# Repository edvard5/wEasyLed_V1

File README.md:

# Addressable RGB LED Controller PCB for WLED

This is a custom PCB designed for controlling addressable RGB LED lights using [WLED](https://github.com/Aircoookie/WLED). The board supports both 5V and 12V LEDs, making it versatile for various setups. It is compact, reliable, and optimized for seamless integration with WLED firmware.

## Features
- Compatible with WLED firmware.
- Supports addressable LEDs (e.g., WS2812, SK6812).
- Integrated voltage regulation for 5V and 12V operation.
- Compact layout with easy connections for power and data.

## Documentation

### PCB Layout

### Schematic

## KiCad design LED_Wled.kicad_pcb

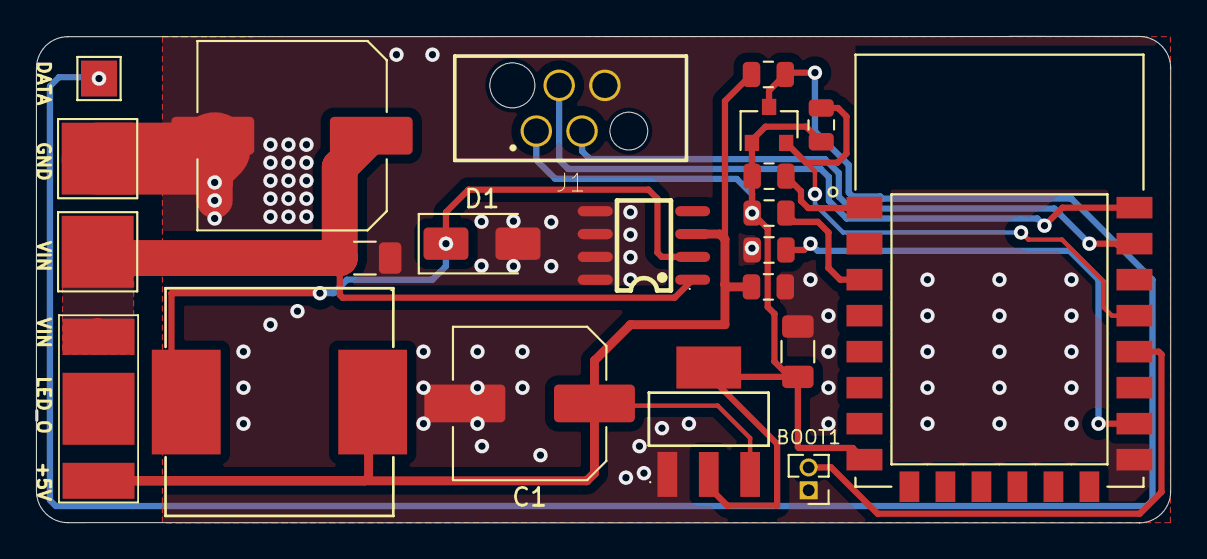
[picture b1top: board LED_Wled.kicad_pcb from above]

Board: 2 copper layers, 63.0 x 27.0 mm, 23 parts (1 on the bottom side), 13 nets.

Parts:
BOOT1: Jumper; PinHeader_1x02_P1.27mm_Vertical
C1: 220uF/35V; C_Elec_8x10.2
C2: 470uF/35V; C_Elec_10x10.2
C3: 1uF/50V; C_1206_3216Metric
C4: 100nF/50V; C_0805_2012Metric
C5: 10uF/50V; C_1206_3216Metric
D1: SS54; D_SMA
J1: SWD_PORT_SKEDD; WR_WST_REDFIT_IDC_4Pin
J2, J4: Conn_01x01; TestPoint_Pad_4.0x4.0mm
J3: Conn_01x01; TestPoint_Pad_2.0x2.0mm
JP1: SolderJumper_3_Open; BIG JUMPER
L1: 68uH; IND-SMD_L12.5-W12.5
Q1: 2N7002; SOT-23
R1, R2, R3, R4, R5: 10k; R_0805_2012Metric
SYM1: LOGO; easyled
U1: ESP8266-12E_ESP-12E; ESP-12E
U2: XL1509; SOIC-8_L5.0-W4.0-P1.27-LS6.0-BL
U3: AMS1117-3.3; SOT-223-3_L6.5-W3.4-P2.30-LS7.0-BR

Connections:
+3V3: C5.1, J1.1, Q1.1 (G), R1.1, R2.2, R4.1, U1.8 (VCC), U3.2 (VOUT), U3.4 (VOUT)
+5V: C1.1, C4.1, JP1.3 (B), L1.2, R5.1, U2.3 (FB), U3.3 (VIN)
GND: BOOT1.1 (A), C1.2, C2.2, C3.2, C4.2, C5.2, D1.2 (A), J1.4, J4.1, R3.2, U1.15 (GND), U2.5 (GND), U2.6 (GND), U2.7 (GND), U2.8 (GND), U3.1 (GND)
LED_OUT_HV: J3.1, Q1.3 (D), R5.2
LED_OUT_LV: Q1.2 (S), R4.2, U1.19 (IO4)
unnamed: BOOT1.2 (B), U1.18 (IO0)
unnamed: D1.1 (K), L1.1, U2.2 (OUTPUT)
unnamed: R1.2, U1.3 (EN)
unnamed: R3.1, U1.16 (IO15)
unnamed: R2.1, U1.1 (RESET)
RXD: J1.3, U1.21 (RXD)
TXD: J1.2, U1.22 (TXD)
VIN: C2.1, C3.1, J2.1, JP1.2 (C), U2.1 (VIN)

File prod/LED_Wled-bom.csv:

"Comment","Designator","Footprint","JLCPCB Part #"
"Jumper","BOOT1","",""
"100nF/50V","C4","0805","C49678"
"10uF/50V","C5","1206","C13585"
"180uF/63V","C1","Radial,10X16mm","C106532"
"1uF/50V","C3","1206","C1848"
"470uF/35V","C2","SMD-ECAP-10x10","C3350"
"SS32","D1","SMC,DO-214AB","C65005"
"Fuse_Small","F1","FUSE-SMD","C220152"
"KF141V-2.54-2P","J2","P=2.54mm","C475114"
"KF141V-2.54-3P","J3","P=2.54mm","C475115"
"SWD_PORT_SKEDD","J1","",""
"68uH","L1","SMD-12.5x12.5x8","C169377"
"BSS138","Q1","SOT-23-3","C400505"
"10k","R1 R2 R3 R4 R5","0805","C17414"
"ESP8266-12E_ESP-12E","U1","DFN-22_16.0x24.0x2.0P","C82891"
"LD1117DT33TR","U3","TO-252-2","C132629"
"XL1509","U2","SOP-8_3.9x4.9x1.27P","C61063"

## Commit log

2021-11-04 library fixes
2021-11-04 rev1.0 release
2021-11-04 rev1.0_PROD
2022-01-12 changing power sch
2022-01-13 updated to rev1.1
2022-01-25 finished rev1.1
2025-01-27 revised pcb, fixed library issues, changed 3.3v component to basic component, added docs and readme
2025-01-28 new release, v1.2, prod files ready
